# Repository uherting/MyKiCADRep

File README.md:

# MyKiCADRep
my works with KiCAD

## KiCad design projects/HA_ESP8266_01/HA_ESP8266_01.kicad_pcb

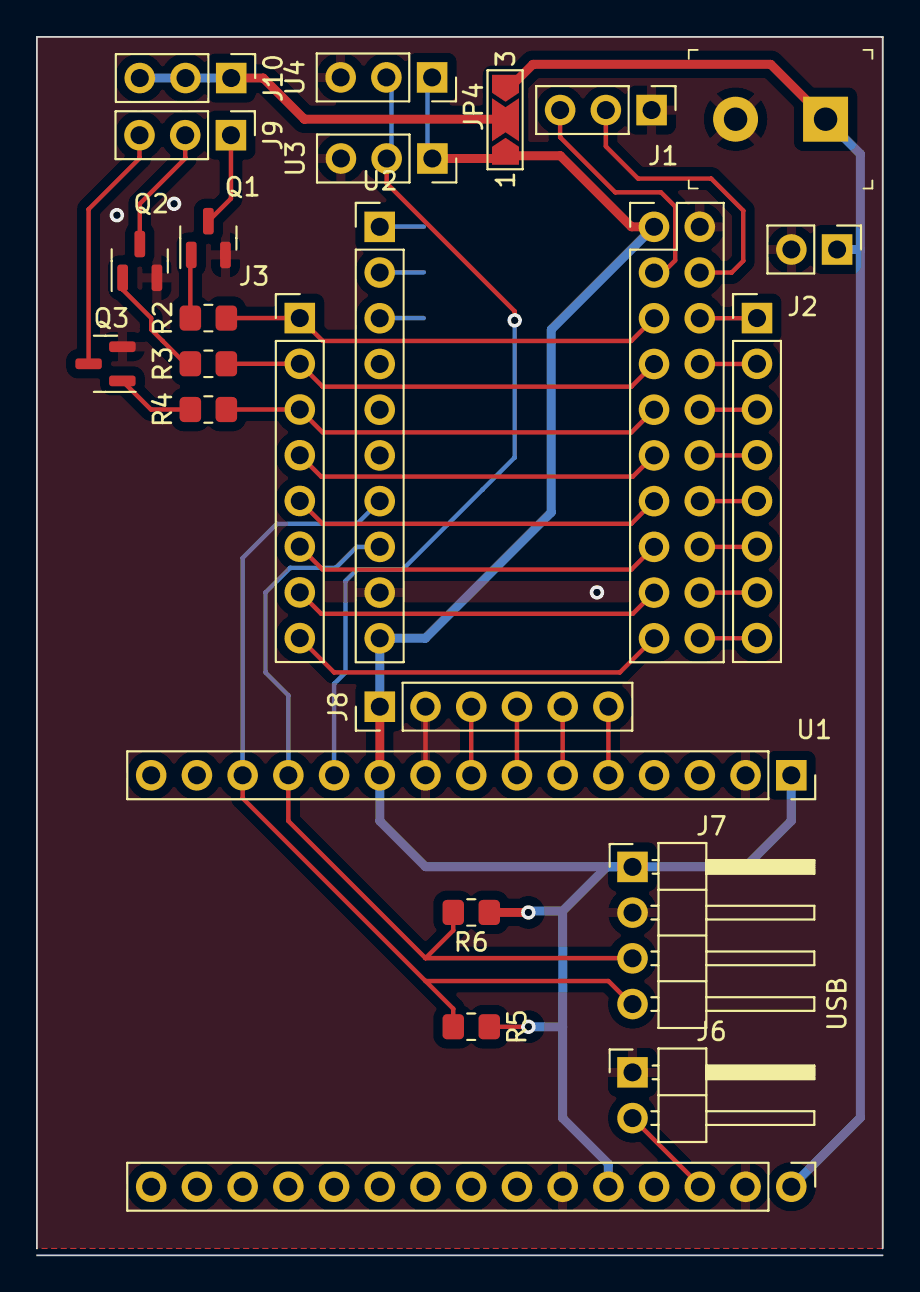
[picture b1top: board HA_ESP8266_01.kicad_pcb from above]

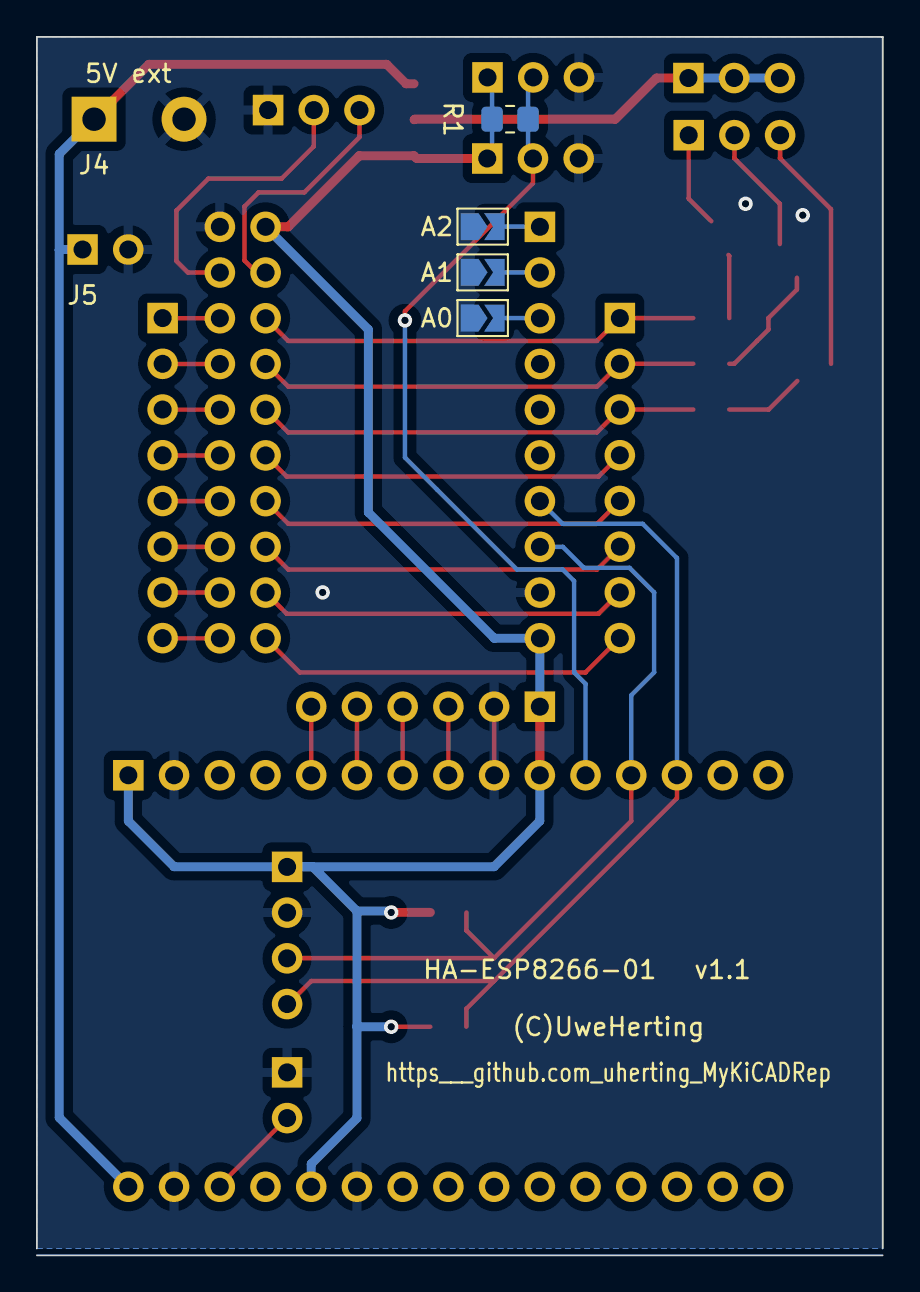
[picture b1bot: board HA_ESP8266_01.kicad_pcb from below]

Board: 2 copper layers, 47.0 x 67.7 mm, 31 parts (8 on the bottom side), 39 nets.

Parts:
J1: IRQs; PinHeader_1x03_P2.54mm_Vertical
J2: DataPort A; PinHeader_1x08_P2.54mm_Vertical
J3: DataPort B; PinHeader_1x08_P2.54mm_Vertical
J4: 5V ext; Term_Block_1x2_P5mm
J5: 5V ext; PinHeader_1x02_P2.54mm_Vertical
J6: ~RESET; PinHeader_1x02_P2.54mm_Horizontal
J7: I2C breakout; PinHeader_1x04_P2.54mm_Horizontal
J8: D5-8 breakout; PinHeader_1x06_P2.54mm_Vertical
J9: SSR out; PinHeader_1x03_P2.54mm_Vertical
J10: SSR VCC; PinHeader_1x03_P2.54mm_Vertical
JP1: A2; SolderJumper-2_P1.3mm_Open_TrianglePad1.0x1.5mm
JP2: A1; SolderJumper-2_P1.3mm_Open_TrianglePad1.0x1.5mm
JP3: A0; SolderJumper-2_P1.3mm_Open_TrianglePad1.0x1.5mm
JP4: SolderJumper_3_Open; SolderJumper-3_P2.0mm_Open_TrianglePad1.0x1.5mm_NumberLabels
Q1, Q2, Q3: MMBT3904; SOT-23
R1, R5, R6: 4k7; R_0805_2012Metric_Pad1.20x1.40mm_HandSolder
R2, R3, R4: 12k; R_0805_2012Metric_Pad1.20x1.40mm_HandSolder
T1: HA-ESP8266-01; PCB_Name
T2: (C)UweHerting; Copyright-Uwe_Herting
T3: https___github.com_uherting_MyKiCADRep; GithubLink_UH
T4: v1.1; PCB_Version
U1: NodeMCU V1; Module_NodeMcu_v1
U2: MCP23017M; Module_MCP23017
U3, U4: 1WireBus

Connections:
1WireData3V3: R1.1, U1.11 (D4), U3.2 (Data), U4.2 (Data)
3V3: J7.1, J8.1, JP4.1 (A), R1.2, R5.1, R6.1, U1.1 (3V3), U1.10 (3V3), U1.20 (3V3), U2.10 (VCC), U2.11 (VCC), U3.1 (3V3), U4.1 (3V3)
5V: J4.1, J5.1, JP4.3 (B), U1.16 (Vin)
B0: J3.1 (P0), R2.2, U2.15 (B0)
B0_OUT: J9.1, Q1.3 (C)
B1: J3.2 (P1), R3.2, U2.17 (B1)
B1_OUT: J9.2, Q2.3 (C)
B2: J3.3 (P2), R4.2, U2.19 (B2)
B2_OUT: J9.3, Q3.3 (C)
D5: J8.3, U1.8 (D5)
D6: J8.4, U1.7 (D6)
D7: J8.5, U1.6 (D7)
D8: J8.6, U1.5 (D8)
GND: J1.1, J4.2, J5.2, J6.1, J7.2, J8.2, JP1.1 (A), JP2.1 (A), JP3.1 (A), Q1.2 (E), Q2.2 (E), Q3.2 (E), U1.2 (GND), U1.9 (GND), U1.17 (GND), U1.21 (GND), U2.9 (GND), U2.12 (GND), U3.3 (GND), U4.3 (GND)
unnamed: J1.2, U2.14 (~ITA)
unnamed: J1.3, U2.13 (~ITB)
unnamed: J2.1 (P0), U2.16 (A0)
unnamed: J2.2 (P1), U2.18 (A1)
unnamed: J2.3 (P2), U2.20 (A2)
unnamed: J2.4 (P3), U2.22 (A3)
unnamed: J2.5 (P4), U2.24 (A4)
unnamed: J2.6 (P5), U2.26 (A5)
unnamed: J2.7 (P6), U2.28 (A6)
unnamed: J2.8 (P7), U2.30 (A7)
unnamed: J3.4 (P3), U2.21 (B3)
unnamed: J3.5 (P4), U2.23 (B4)
unnamed: J3.6 (P5), U2.25 (B5)
unnamed: J3.7 (P6), U2.27 (B6)
unnamed: J3.8 (P7), U2.29 (B7)
unnamed: J10.1, J10.2, J10.3, JP4.2 (C)
unnamed: JP1.2 (B), U2.1 (ADDR2)
unnamed: JP2.2 (B), U2.2 (ADDR1)
unnamed: JP3.2 (B), U2.3 (ADDR0)
unnamed: Q1.1 (B), R2.1
unnamed: Q2.1 (B), R3.1
unnamed: Q3.1 (B), R4.1
SCL: J7.3, R6.2, U1.12 (D3), U2.8 (SCL/SCK)
SDA: J7.4, R5.2, U1.13 (D2), U2.7 (SDA/SI)
~RST: J6.2, U1.18 (~RST)

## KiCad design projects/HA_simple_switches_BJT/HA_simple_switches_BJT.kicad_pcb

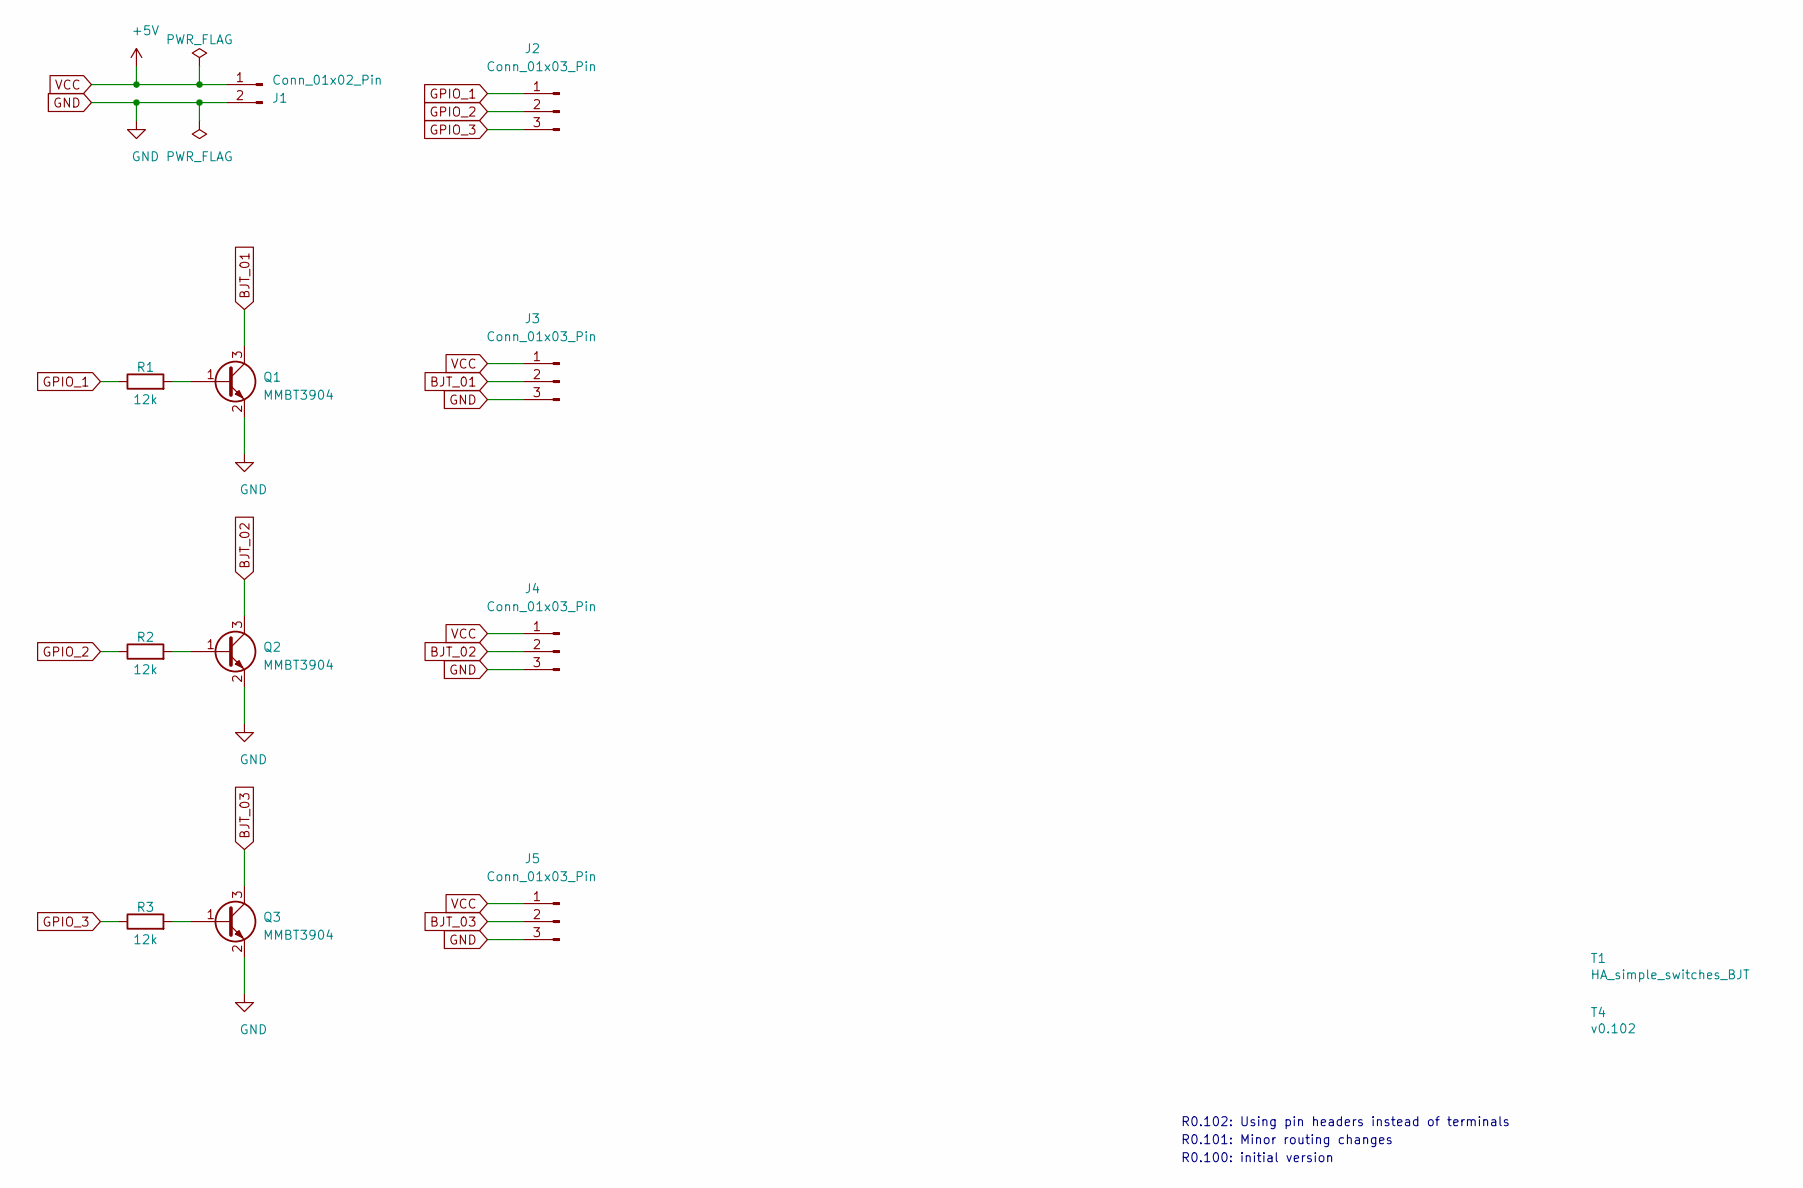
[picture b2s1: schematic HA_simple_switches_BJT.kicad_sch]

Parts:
J1: Conn_01x02_Pin; PinHeader_1x02_P2.54mm_Vertical
J2, J3, J4, J5: Conn_01x03_Pin; PinHeader_1x03_P2.54mm_Vertical
Q1, Q2, Q3: MMBT3904; SOT-23
R1, R2, R3: 12k; R_0805_2012Metric_Pad1.20x1.40mm_HandSolder
T1: HA_simple_switches_BJT; PCB_Name
T4: v0.102; PCB_Version

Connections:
BJT_01: J3.2, Q1.3 (C)
BJT_02: J4.2, Q2.3 (C)
BJT_03: J5.2, Q3.3 (C)
GND: J1.2, J3.3, J4.3, J5.3, Q1.2 (E), Q2.2 (E), Q3.2 (E)
GPIO_1: J2.1, R1.1
GPIO_2: J2.2, R2.1
GPIO_3: J2.3, R3.1
unnamed: Q1.1 (B), R1.2
unnamed: Q2.1 (B), R2.2
unnamed: Q3.1 (B), R3.2
VCC: J1.1, J3.1, J4.1, J5.1

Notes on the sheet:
R0.102: Using pin headers instead of terminals
R0.100: initial version
R0.101: Minor routing changes

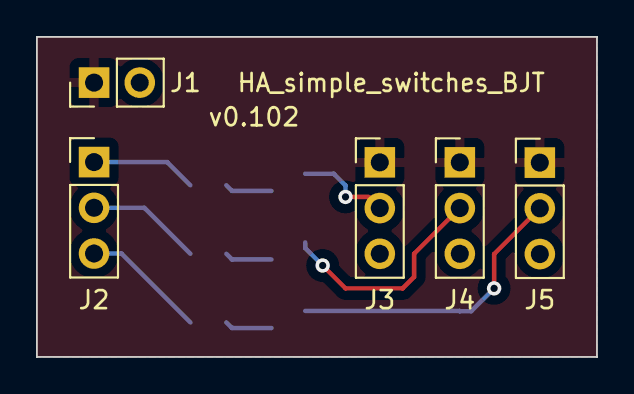
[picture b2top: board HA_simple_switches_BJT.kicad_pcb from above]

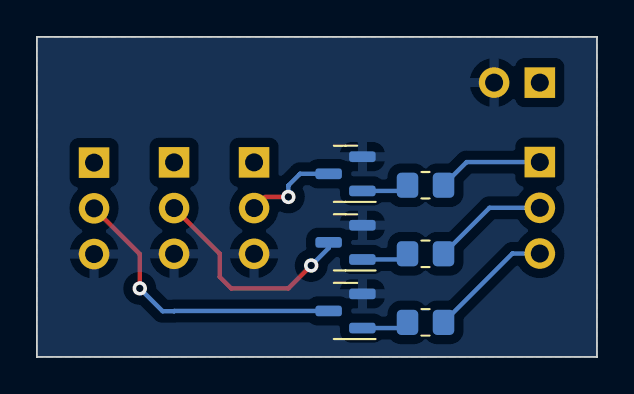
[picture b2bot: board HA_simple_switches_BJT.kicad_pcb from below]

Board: 2 copper layers, 31.1 x 17.8 mm, 13 parts (6 on the bottom side), 11 nets.

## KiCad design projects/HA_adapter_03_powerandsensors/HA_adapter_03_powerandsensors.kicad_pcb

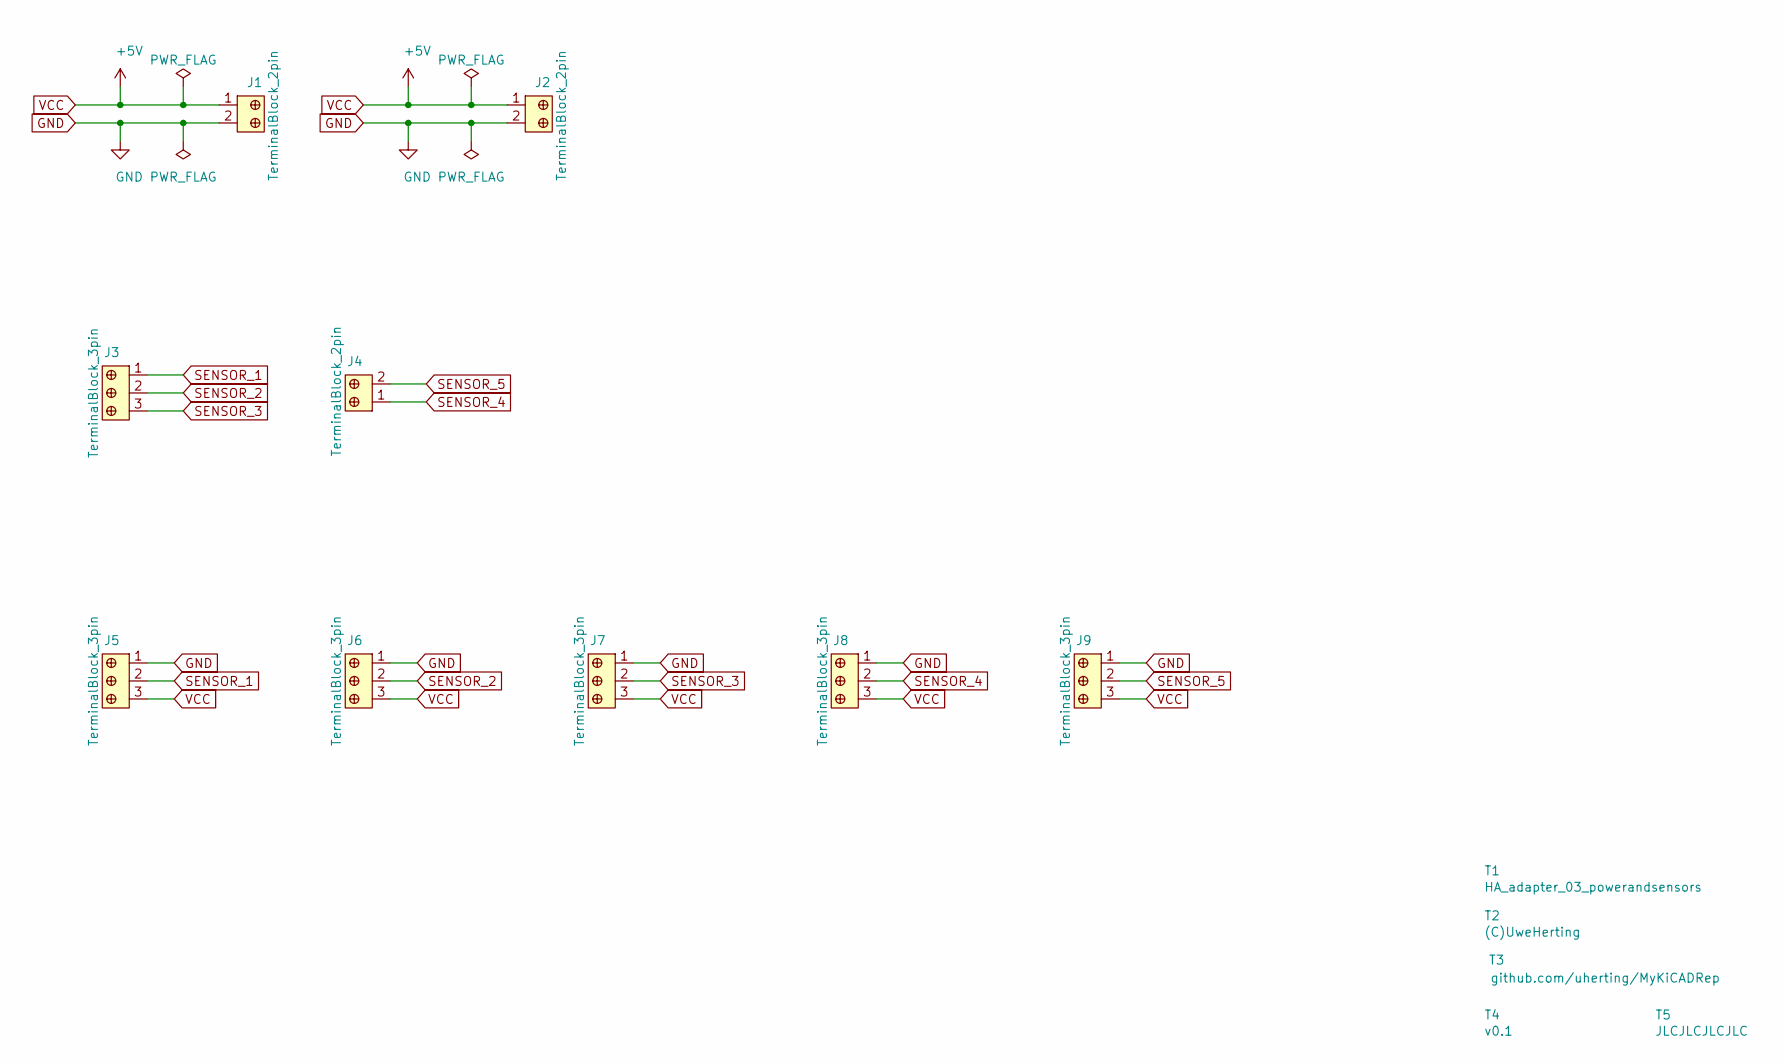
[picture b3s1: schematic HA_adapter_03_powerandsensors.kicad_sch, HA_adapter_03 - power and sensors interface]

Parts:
J1, J2, J4: TerminalBlock_2pin; Term_Block_1x2_P5mm; MPN OSTTC020162; Digi-Key_PN ED2600-ND
J3, J5, J6, J7, J8, J9: TerminalBlock_3pin; Term_Block_1x3_P5mm; MPN OSTTC030162; Digi-Key_PN ED2601-ND
T1: HA_adapter_03_powerandsensors; PCB_Name
T2: (C)UweHerting; Copyright-Uwe_Herting
T3: github.com/uherting/MyKiCADRep; GithubLink_UH
T4: v0.1; PCB_Version
T5: JLCJLCJLCJLC; PCB_Version

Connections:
GND: J1.2, J2.2, J5.1, J6.1, J7.1, J8.1, J9.1
SENSOR_1: J3.1, J5.2
SENSOR_2: J3.2, J6.2
SENSOR_3: J3.3, J7.2
SENSOR_4: J4.1, J8.2
SENSOR_5: J4.2, J9.2
VCC: J1.1, J2.1, J5.3, J6.3, J7.3, J8.3, J9.3

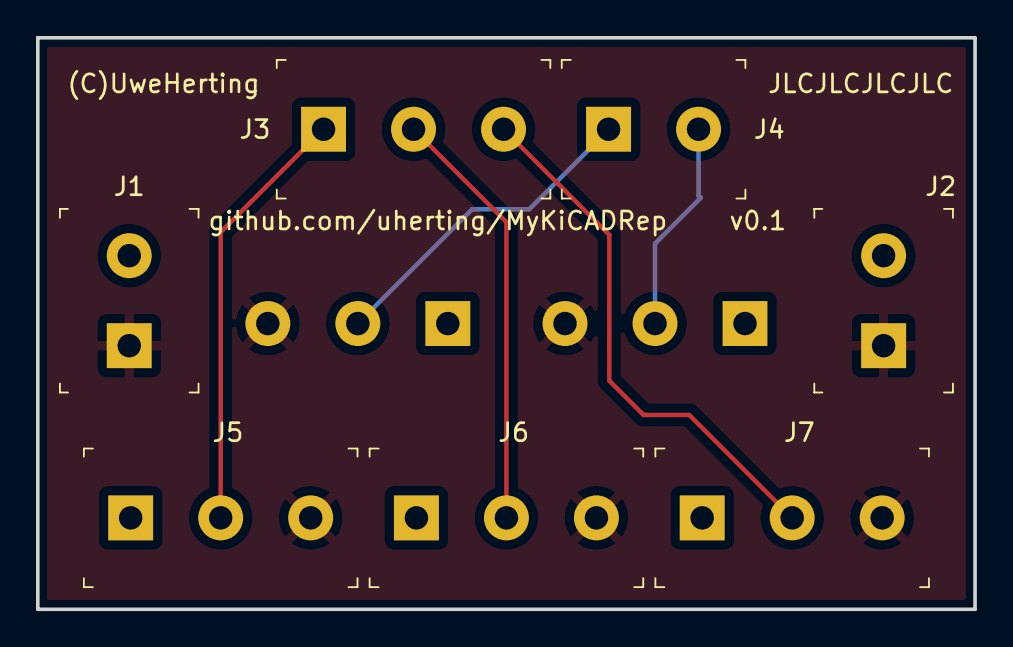
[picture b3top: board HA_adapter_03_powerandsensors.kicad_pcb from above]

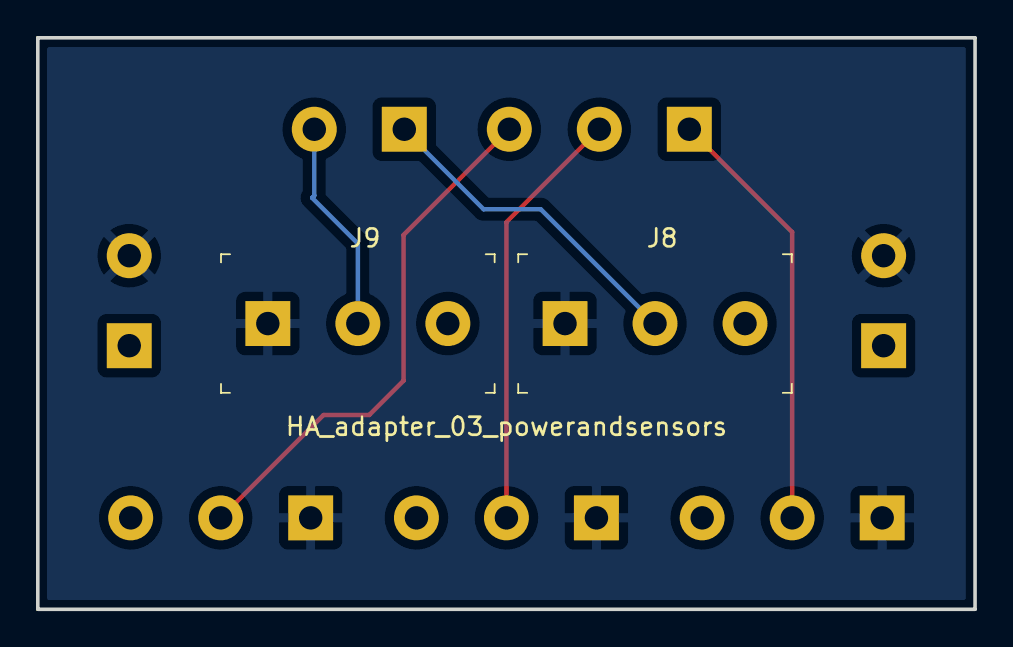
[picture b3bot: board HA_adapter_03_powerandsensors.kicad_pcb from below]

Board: 2 copper layers, 52.1 x 31.7 mm, 14 parts (2 on the bottom side), 7 nets.

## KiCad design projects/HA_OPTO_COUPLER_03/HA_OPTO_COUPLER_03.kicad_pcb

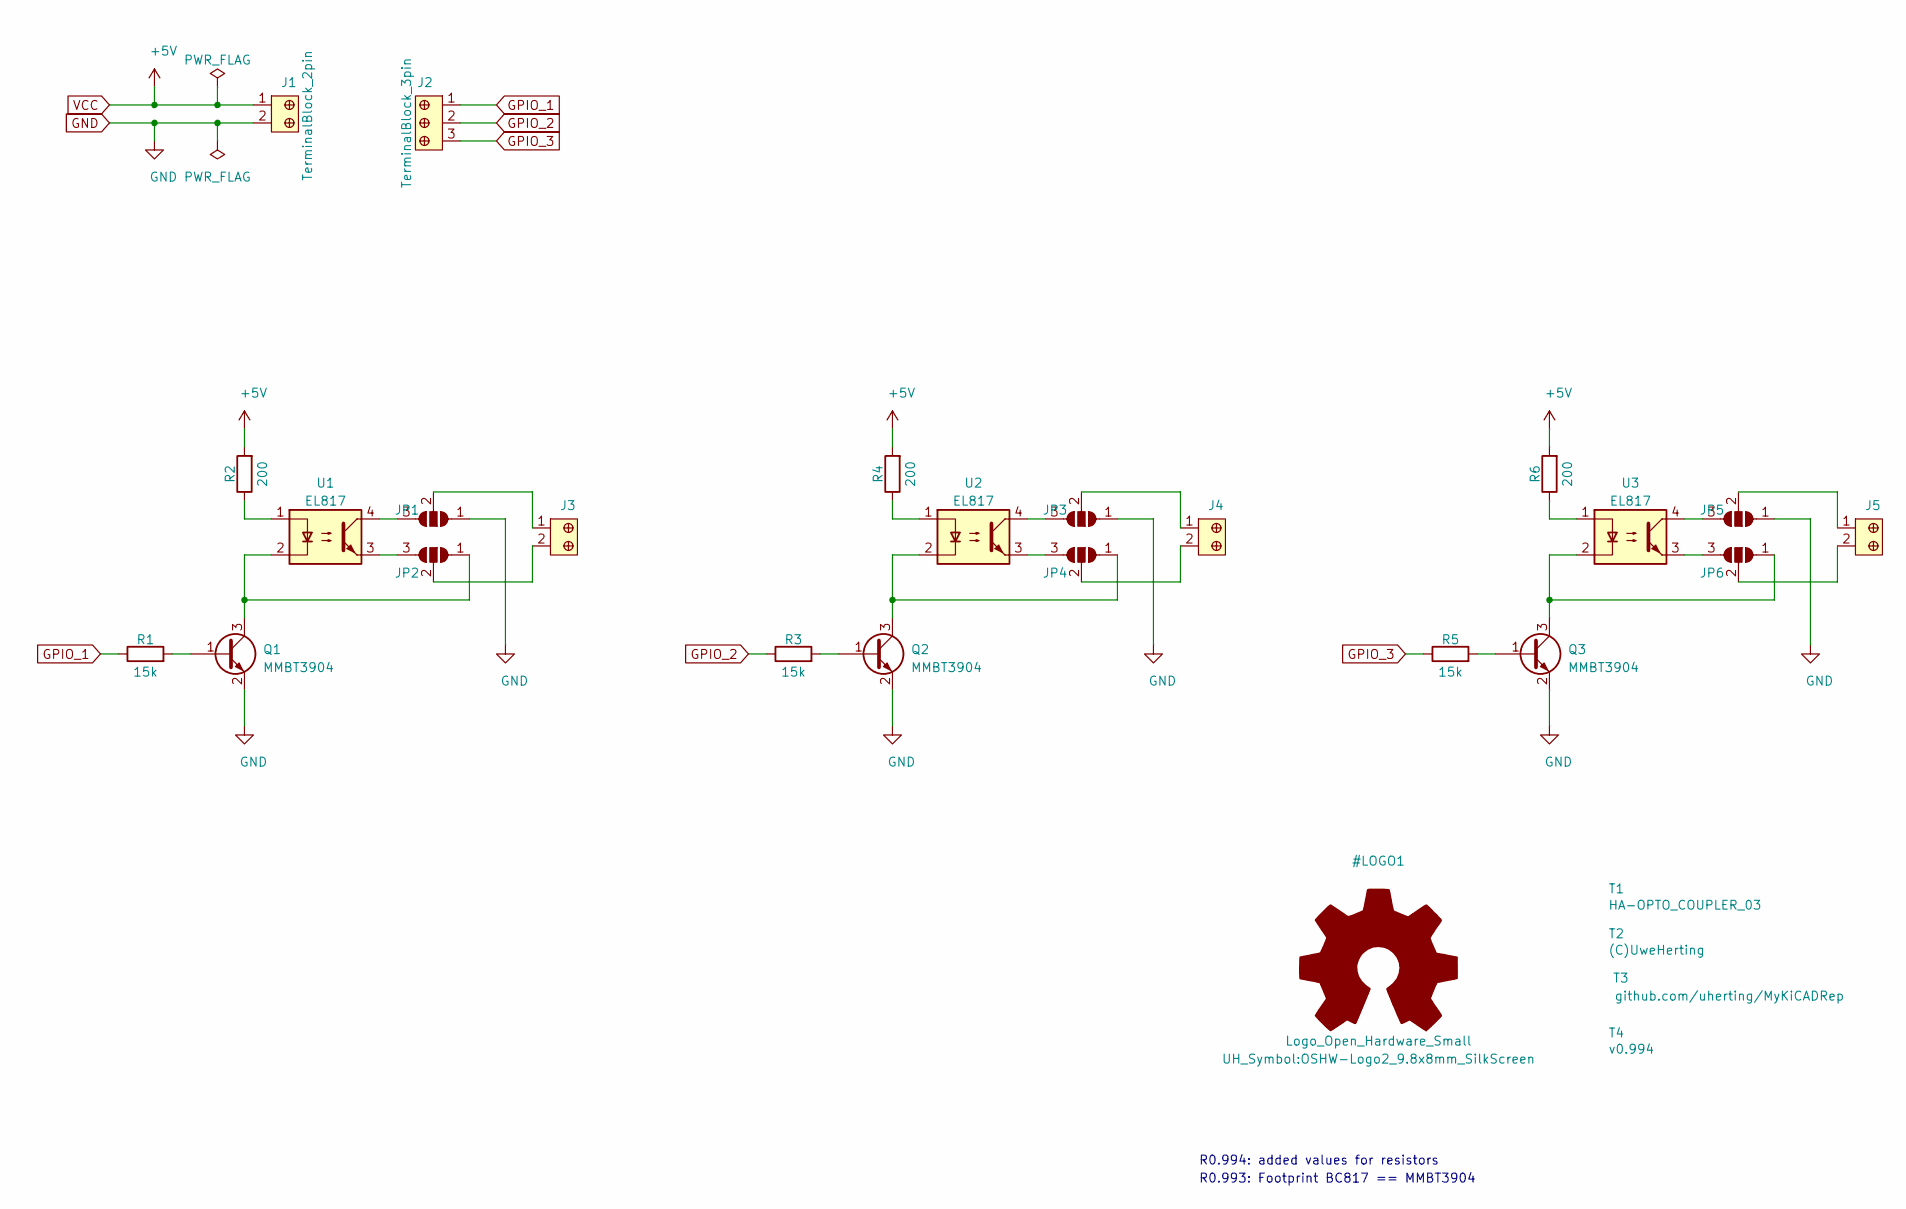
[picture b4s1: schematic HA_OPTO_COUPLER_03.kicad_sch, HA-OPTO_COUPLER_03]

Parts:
J1, J3, J4, J5: TerminalBlock_2pin; Term_Block_1x2_P5mm; MPN OSTTC020162; Digi-Key_PN ED2600-ND
J2: TerminalBlock_3pin; Term_Block_1x3_P5mm; MPN OSTTC030162; Digi-Key_PN ED2601-ND
JP1, JP2, JP3, JP4, JP5, JP6: SolderJumper_3_Open; SolderJumper-3_P2.0mm_Open_TrianglePad1.0x1.5mm_NumberLabels
Q1, Q2, Q3: MMBT3904; SOT-23
R1, R3, R5: 15k; R_0805_2012Metric_Pad1.20x1.40mm_HandSolder
R2, R4, R6: 200; R_0805_2012Metric_Pad1.20x1.40mm_HandSolder
T1: HA-OPTO_COUPLER_03; PCB_Name
T2: (C)UweHerting; Copyright-Uwe_Herting
T3: github.com/uherting/MyKiCADRep; GithubLink_UH
T4: v0.994; PCB_Version
U1, U2, U3: EL817; EL817-S1T

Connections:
GND: J1.2, JP1.1 (A), JP3.1 (A), JP5.1 (A), Q1.2 (E), Q2.2 (E), Q3.2 (E)
GPIO_1: J2.1, R1.1
GPIO_2: J2.2, R3.1
GPIO_3: J2.3, R5.1
unnamed: J3.1, JP1.2 (C)
unnamed: J3.2, JP2.2 (C)
unnamed: J4.1, JP3.2 (C)
unnamed: J4.2, JP4.2 (C)
unnamed: J5.1, JP5.2 (C)
unnamed: J5.2, JP6.2 (C)
unnamed: JP1.3 (B), U1.4
unnamed: JP2.1 (A), Q1.3 (C), U1.2
unnamed: JP2.3 (B), U1.3
unnamed: JP3.3 (B), U2.4
unnamed: JP4.1 (A), Q2.3 (C), U2.2
unnamed: JP4.3 (B), U2.3
unnamed: JP5.3 (B), U3.4
unnamed: JP6.1 (A), Q3.3 (C), U3.2
unnamed: JP6.3 (B), U3.3
unnamed: Q1.1 (B), R1.2
unnamed: Q2.1 (B), R3.2
unnamed: Q3.1 (B), R5.2
unnamed: R2.1, U1.1
unnamed: R4.1, U2.1
unnamed: R6.1, U3.1
VCC: J1.1, R2.2, R4.2, R6.2

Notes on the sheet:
R0.994: added values for resistors
R0.993: Footprint BC817 == MMBT3904

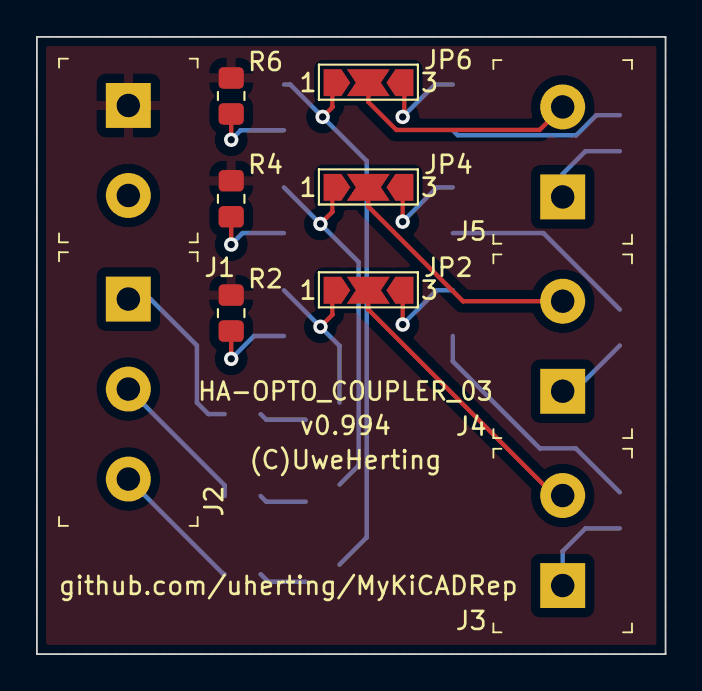
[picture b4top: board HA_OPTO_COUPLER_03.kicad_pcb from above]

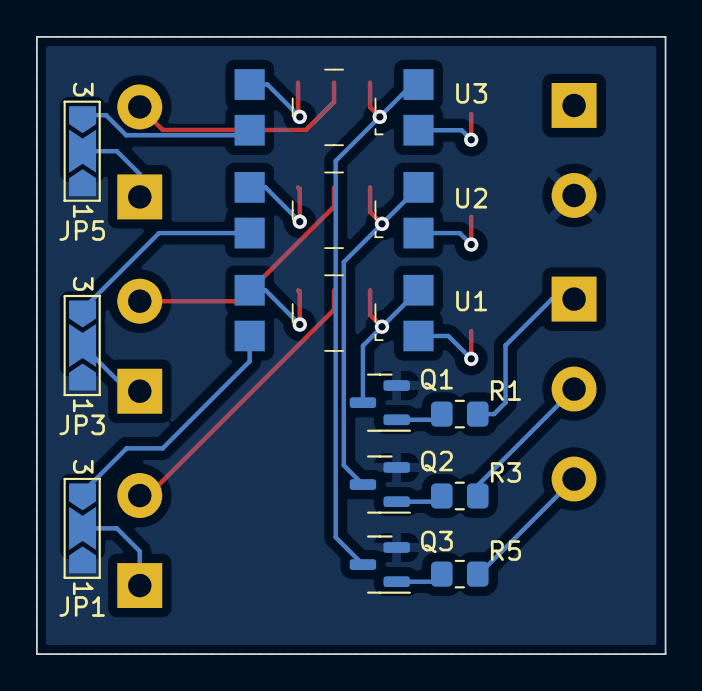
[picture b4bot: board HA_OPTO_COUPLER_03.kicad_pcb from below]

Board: 2 copper layers, 34.9 x 34.3 mm, 27 parts (12 on the bottom side), 26 nets.

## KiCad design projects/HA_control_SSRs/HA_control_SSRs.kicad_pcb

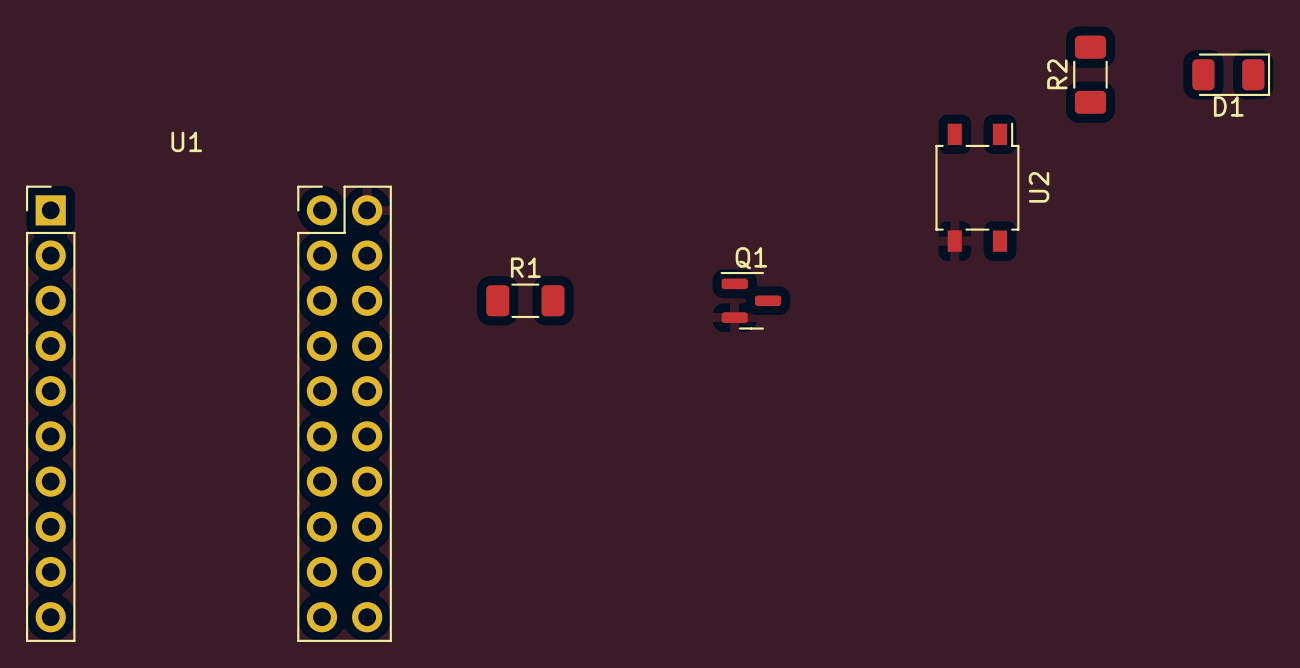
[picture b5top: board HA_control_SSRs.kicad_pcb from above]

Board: 2 copper layers, 6 parts (0 on the bottom side), 7 nets, no tracks yet.

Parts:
D1: IR26-21C_L110_TR8; LED_1206_3216Metric
Q1: MMBT3904; SOT-23
R1, R2: 1k; R_1206_3216Metric_Pad1.30x1.75mm_HandSolder
U1: MCP23017M; Module_MCP23017
U2: ASSR-1218; SO-4_4.4x4.3mm_P2.54mm

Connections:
+5V: R2.1, U2.1
GND: Q1.2 (E), U1.12 (GND), U2.3
unnamed: D1.1 (K), U2.4
unnamed: D1.2 (A), R2.2
unnamed: Q1.1 (B), R1.2
unnamed: Q1.3 (C), U2.2
unnamed: R1.1, U1.15 (B0)

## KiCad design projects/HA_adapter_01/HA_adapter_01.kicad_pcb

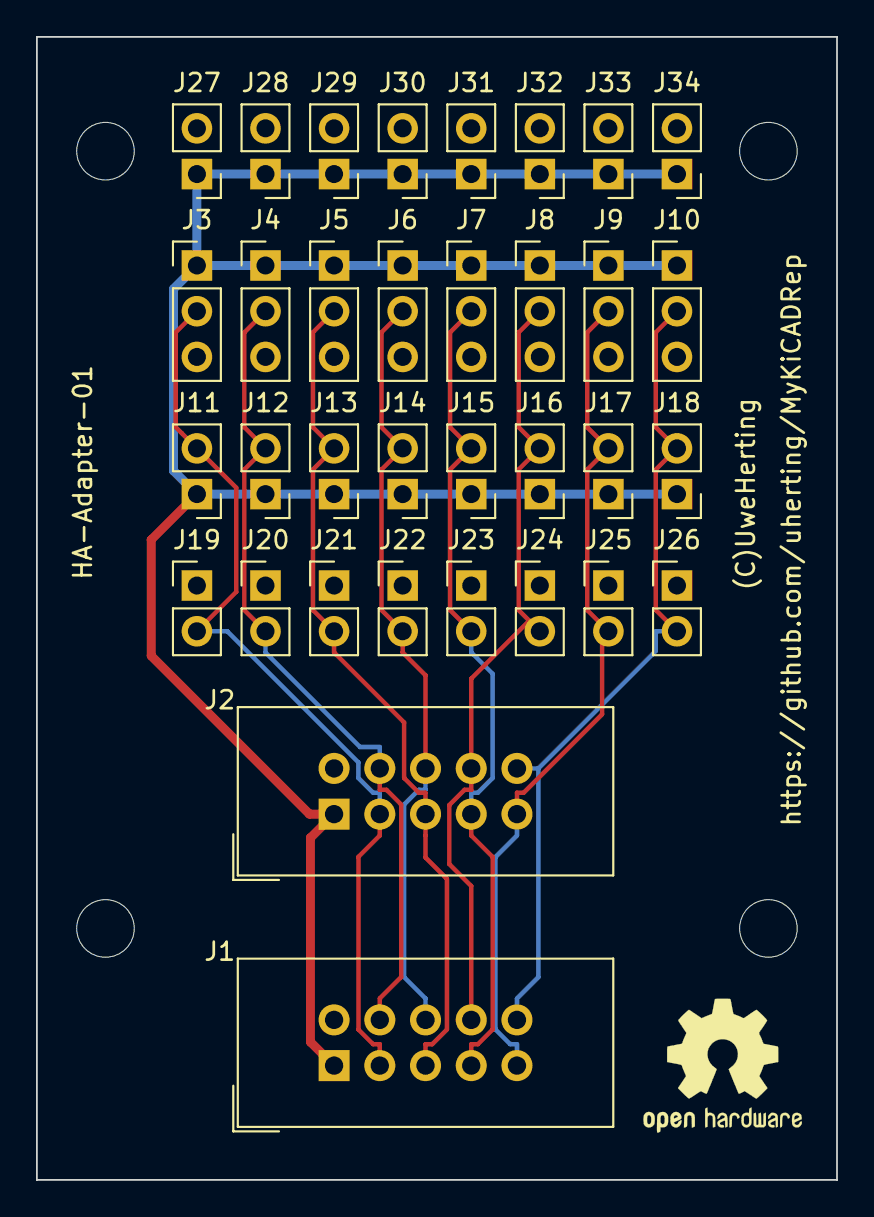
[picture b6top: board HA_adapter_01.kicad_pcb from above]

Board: 2 copper layers, 44.4 x 63.5 mm, 42 parts (0 on the bottom side), 10 nets.

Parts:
H1, H2, H3, H4: MountingHole; MountingHole_3.2mm_M3_ISO7380
J1, J2: PWR_SIGs; IDC-Header_2x05_P2.54mm_Vertical
J3, J4, J5, J6, J7, J8, J9, J10: P_SIG; PinHeader_1x03_P2.54mm_Vertical
J11, J12, J13, J14, J15, J16, J17, J18: VCC_SIG; PinHeader_1x02_P2.54mm_Vertical
J19, J20, J21, J22, J23, J24, J25, J26: GND_SIG; PinHeader_1x02_P2.54mm_Vertical
J27, J28, J29, J30, J31, J32, J33, J34: PWR; PinHeader_1x02_P2.54mm_Vertical
LOGO1: Logo_Open_Hardware_Small; OSHW-Logo2_9.8x8mm_SilkScreen
T1: HA-Adapter-01; PCB_Name
T2: (C)UweHerting; Copyright-Uwe_Herting
T3: https://github.com/uherting/MyKiCADRep; GithubLink_UH

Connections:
/5V: J1.1, J2.1, J3.1, J4.1, J5.1, J6.1, J7.1, J8.1, J9.1, J10.1, J11.1, J12.1, J13.1, J14.1, J15.1, J16.1, J17.1, J18.1, J27.1, J28.1, J29.1, J30.1, J31.1, J32.1, J33.1, J34.1
/GND: J1.2, J2.2, J3.3, J4.3, J5.3, J6.3, J7.3, J8.3, J9.3, J10.3, J19.1, J20.1, J21.1, J22.1, J23.1, J24.1, J25.1, J26.1, J27.2, J28.2, J29.2, J30.2, J31.2, J32.2, J33.2, J34.2
/S1: J1.3, J2.3, J3.2, J11.2, J19.2
/S2: J1.4, J2.4, J4.2, J12.2, J20.2
/S3: J1.5, J2.5, J5.2, J13.2, J21.2
/S4: J1.6, J2.6, J6.2, J14.2, J22.2
/S5: J1.7, J2.7, J7.2, J15.2, J23.2
/S6: J1.8, J2.8, J8.2, J16.2, J24.2
/S7: J1.9, J2.9, J9.2, J17.2, J25.2
/S8: J1.10, J2.10, J10.2, J18.2, J26.2

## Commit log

2019-10-11 adding files
2020-01-26 redesigned PCB
2020-02-08 updated schema and PCB
2021-03-24 snapshot
2021-04-10 added empty HA_OPTO_COUPLER_02 project
2021-04-17 snapshot after creating gerber files for HA_OPTO_COUPLER_02
2021-04-18 snapshot after HA_OPTO_COUPLER_03 is ready for prod
2021-04-18 cleanup
2021-04-18 added grbjob files to ignore
2021-04-19 added location for JLCPCB ref num and minor cleanup
2021-04-19 snapshot of project HA_ESP8266_01 before modifications
2021-04-19 snapshot, addded HA_ESP8266_01/plots.zip
2021-04-22 added symlinks (to be used to upload for manufacturing) pointing to the standard plots.zip
2021-04-22 updating BOM and production files of pcbs of HA_ESP8266_01 and HA_OPTO_COUPLER_03
2021-08-26 snapshot after cleaning HA_OPTO_COUPLER_03 project
2021-08-26 HA_OPTO_COUPLER_03: changed values for R1, R3, R5
2021-09-18 added description for solder jumpers
2021-09-29 added current version of HA_adapter_03_powerandsensors project and updated files
2021-11-28 snapshot prior to changing HA_ESP8266_01 (removing 3pin for one IO and adding 4k7 for dallas 18b20 sensor)
2022-09-21 updated projects HA_OPTO_COUPLER_03 and HA_adapter_03_powerandsensors
2022-09-21 added project HA_simple_switches_BJT
2022-10-02 v101 minor routing changes
